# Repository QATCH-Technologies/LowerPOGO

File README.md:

# LowerPOGO
KiCad model for lower pogo design on 4x6 system

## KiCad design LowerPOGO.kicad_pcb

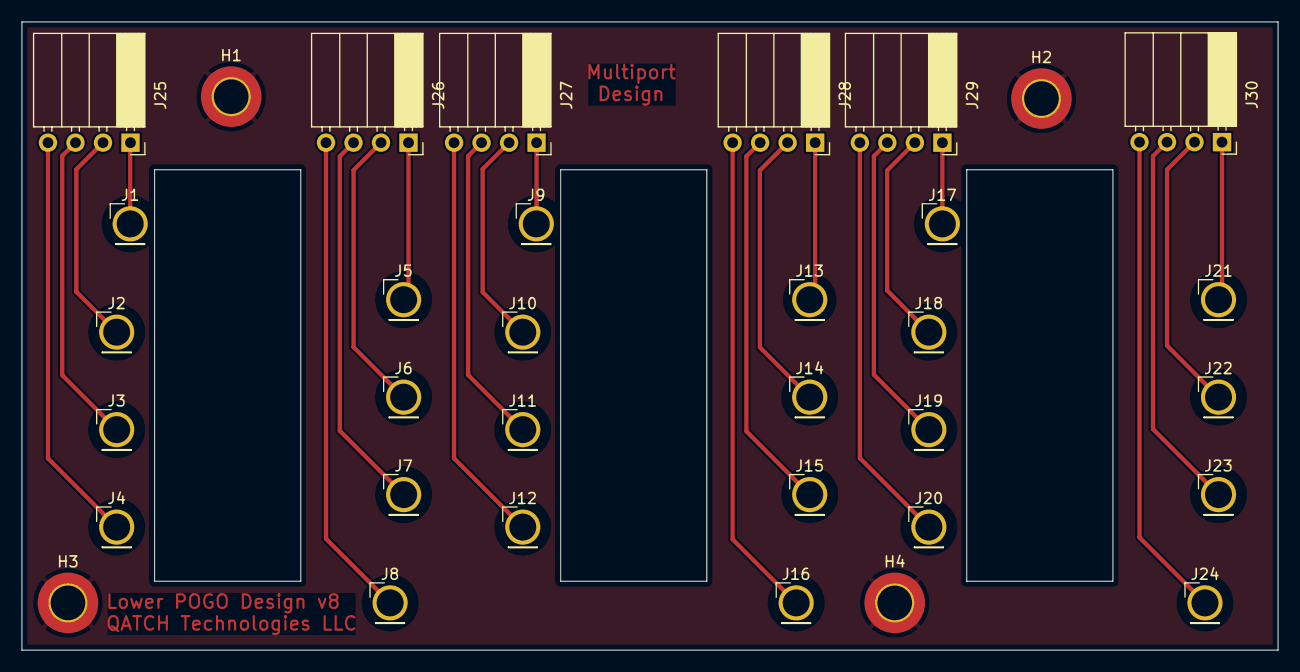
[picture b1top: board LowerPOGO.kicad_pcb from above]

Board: 2 copper layers, 116.0 x 58.0 mm, 34 parts (0 on the bottom side), 25 nets.

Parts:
H1, H2, H3, H4: MountingHole_Pad; MountingHole_3.2mm_M3_DIN965_Pad_TopBottom
J1, J2, J3, J4, J5, J6, J7, J8, J9, J10, J11, J12, J13, J14, J15, J16, J17, J18, J19, J20, J21, J22, J23, J24: Conn_01x01_MountingPin; PinHeader_1x01_D2.54mm_Vertical_PogoPin
J25, J26, J27, J28, J29, J30: Conn_01x04_Pin; PinSocket_1x04_P2.54mm_Horizontal

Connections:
Earth: H1.1, H2.1, H3.1, H4.1
unnamed: J1.1, J25.1
unnamed: J2.1, J25.2
unnamed: J10.1, J27.2
unnamed: J11.1, J27.3
unnamed: J12.1, J27.4
unnamed: J13.1, J28.1
unnamed: J14.1, J28.2
unnamed: J15.1, J28.3
unnamed: J16.1, J28.4
unnamed: J17.1, J29.1
unnamed: J18.1, J29.2
unnamed: J19.1, J29.3
unnamed: J20.1, J29.4
unnamed: J21.1, J30.1
unnamed: J22.1, J30.2
unnamed: J23.1, J30.3
unnamed: J24.1, J30.4
unnamed: J3.1, J25.3
unnamed: J4.1, J25.4
unnamed: J5.1, J26.1
unnamed: J6.1, J26.2
unnamed: J7.1, J26.3
unnamed: J8.1, J26.4
unnamed: J9.1, J27.1

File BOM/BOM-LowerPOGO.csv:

"Id";"Designator";"Footprint";"Quantity";"DigiKey Part Number";"Manufacturer Product Number";
1;"J21,J7,J8,J10,J14,J22,J11,J12,J1,J20,J5,J18,J2,J3,J6,J17,J4,J24,J23,J9,J16,J19,J13,J15";"PinHeader_1x01_P2.53mm_Vertical";24;"ED10089-ND";"0859-0-15-20-82-14-11-0";
2;"J25";"PinSocket_2x12_P2.54mm_Horizontal";1;"S5526-ND";"PPTC122LJBN-RC";

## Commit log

2024-05-16 Initial commit of KiCad project for LowerPOGO
2024-05-16 Add fabrication outputs for lowerPOGO v3 design
2024-05-21 Add BOM and Pick and Place
2024-05-21 Update rev3 to modify J25 connector: Move J25 to be populated from the back of board Updated SVGs to show component 3D models Updated Fabrication Outputs
2024-06-21 LowerPOGO v4 (2024-06-21) Resize J vias for proper fit inner diameter: 2.49mm outer diameter: 3.25mm
2024-08-26 LowerPOGO v5 1mm trace spacing 1mm POGO clearance
2024-08-29 Add Extra Assets to v5: Update copper layer SVGs Add Edge Cuts SVG image Add Dimensional Drawings
2024-09-11 Update Drill, Gerber, and Pick and Place Fabrication Outputs for V5
2024-09-11 Update SVGs and create v5 output files
2024-09-30 Changes for LowerPOGO v6: - Move the 3 cutouts left 2.5mm - Reduce cutout height by 1.5mm - Move center port right 0.25mm - Move traces for moved cutouts - Set clearance to avoid island - Update vers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
2024-09-30 Add fabrication outputs for LowerPOGO v6 changes
2025-04-10 Pushing local changes before branching
2025-04-10 Update KiCad designs for LowerPOGO to Multiport Design (v7) Tag fabrication outputs for this revision, remove Drawings.
2025-07-31 LowerPOGO v8 Changes: - Flip lower POGO design for modified sensor layout
2025-07-31 Resave files for new KiCad v9 format
